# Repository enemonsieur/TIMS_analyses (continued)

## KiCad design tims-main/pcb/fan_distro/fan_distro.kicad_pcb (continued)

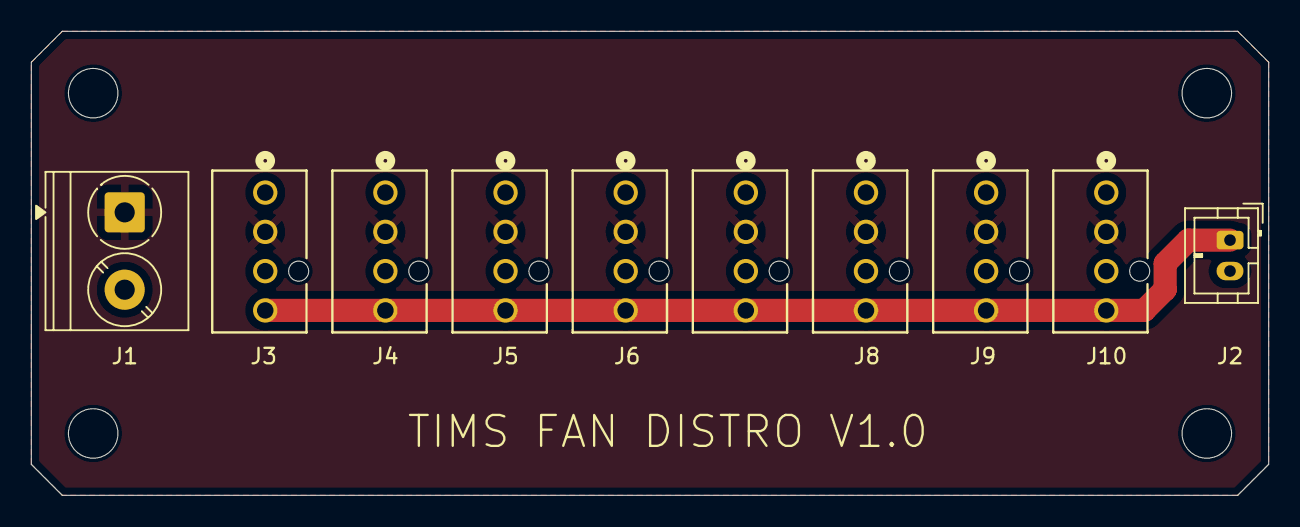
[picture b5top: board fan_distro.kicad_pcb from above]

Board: 2 copper layers, 80.0 x 30.0 mm, 10 parts (0 on the bottom side), 3 nets.

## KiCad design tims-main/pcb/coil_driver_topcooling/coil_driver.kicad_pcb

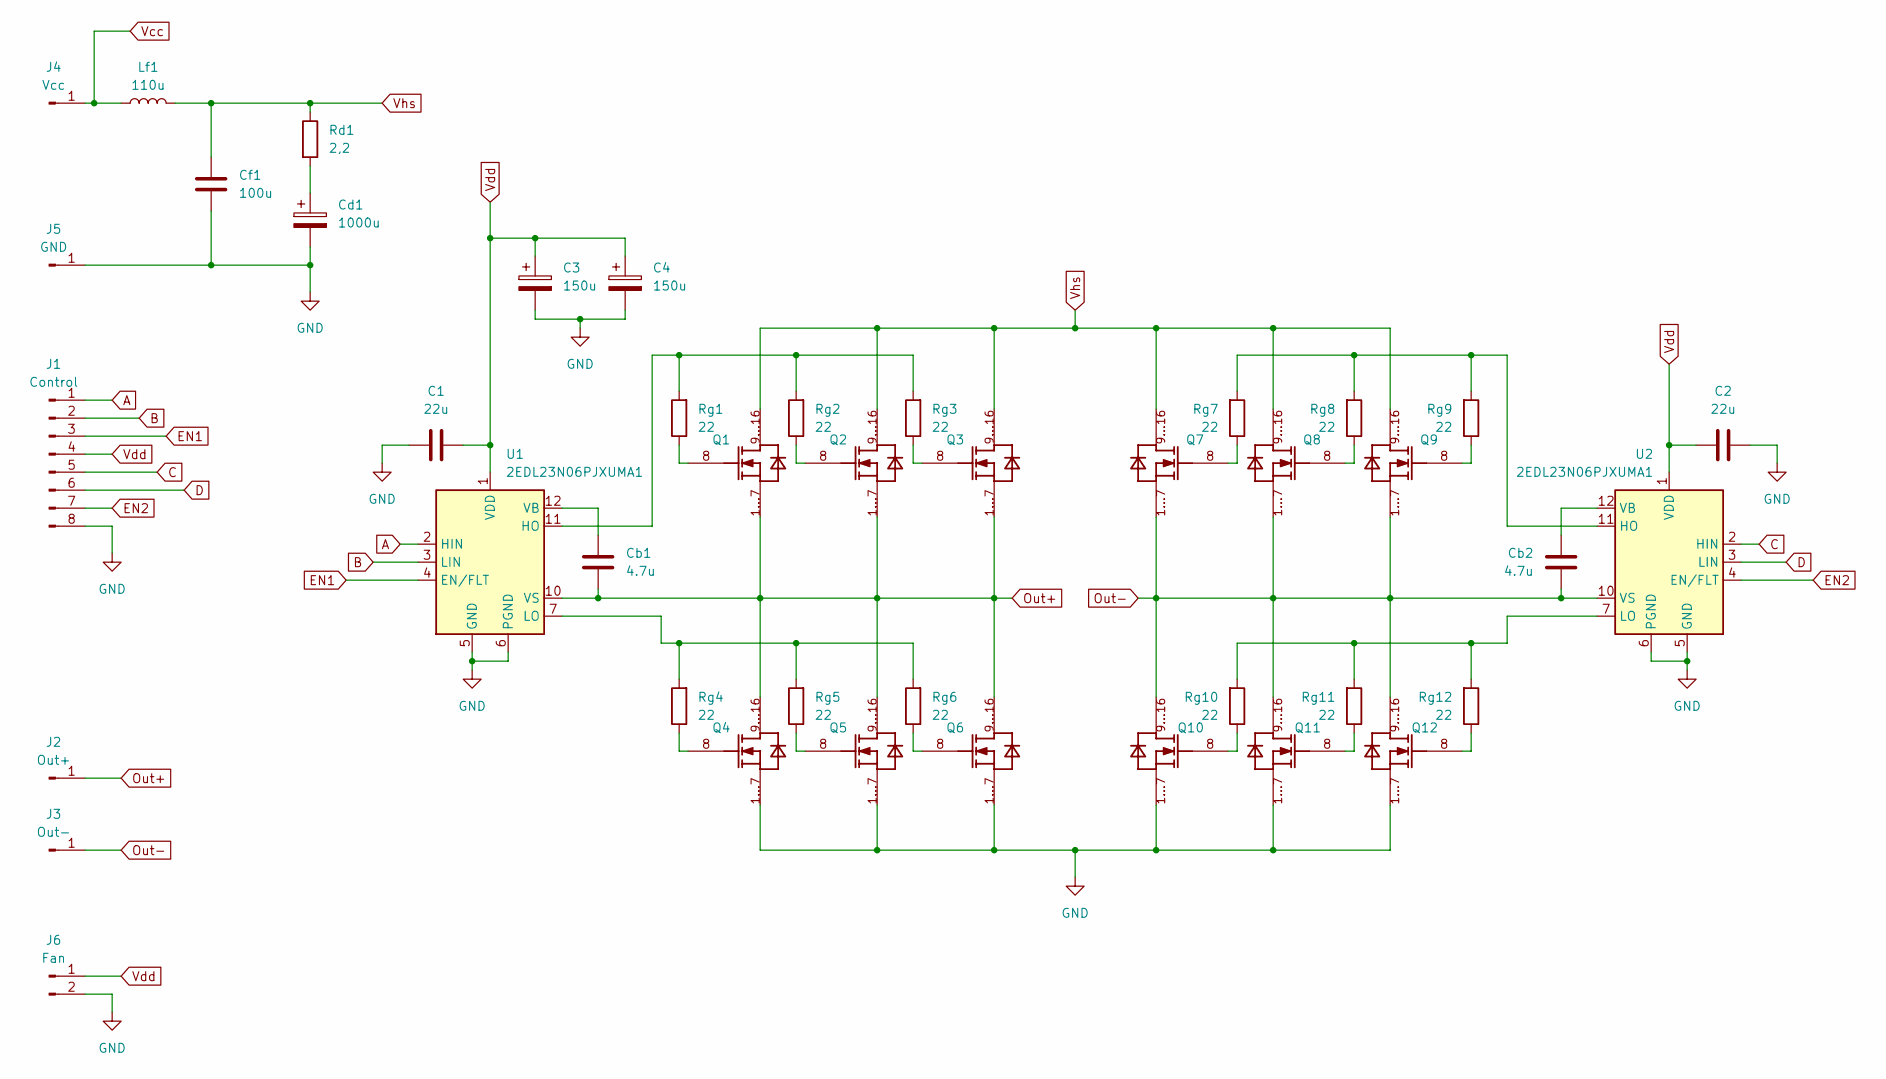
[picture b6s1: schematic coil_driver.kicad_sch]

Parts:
C1, C2: 22u; C_1206_3216Metric
C3, C4: 150u; CP_Radial_D10.0mm_P5.00mm
Cb1, Cb2: 4.7u; C_1206_3216Metric
Cd1: 1000u; CP_Radial_D30.0mm_P10.00mm_SnapIn
Cf1: 100u; 944U101K801AAM
J1: Control; JST_PH_B8B-PH-K_1x08_P2.00mm_Vertical
J2: Out+; Power_Pad
J3: Out-; Power_Pad
J4: Vcc; Power_Pad
J5: GND; Power_Pad
J6: Fan; JST_PH_B2B-PH-K_1x02_P2.00mm_Vertical
Lf1: 110u; IND_CPEX3635L-111MC
Q1, Q2, Q3, Q4, Q5, Q6, Q7, Q8, Q9, Q10, Q11, Q12: IPTC068N20NM6; SOIC120P1500X235-16N-1-V
Rd1: 2,2; SQMBW102R2J
Rg1, Rg2, Rg3, Rg4, Rg5, Rg6, Rg7, Rg8, Rg9, Rg10, Rg11, Rg12: 22; R_1206_3216Metric
U1, U2: 2EDL23N06PJXUMA1; SOIC-14_3.9x8.7mm_P1.27mm

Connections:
A: J1.1, U1.2 (HIN)
B: J1.2, U1.3 (LIN)
C: J1.5, U2.2 (HIN)
D: J1.6, U2.3 (LIN)
EN1: J1.3, U1.4 (EN/FLT)
EN2: J1.7, U2.4 (EN/FLT)
GND: C1.1, C2.1, C3.2, C4.2, Cd1.2, Cf1.2, J1.8, J5.1, J6.2, Q4.1 (S1), Q4.2 (S2), Q4.3 (S3), Q4.4 (S4), Q4.5 (S5), Q4.6 (S6), Q4.7 (S7), Q5.1 (S1), Q5.2 (S2), Q5.3 (S3), Q5.4 (S4), Q5.5 (S5), Q5.6 (S6), Q5.7 (S7), Q6.1 (S1), Q6.2 (S2), Q6.3 (S3), Q6.4 (S4), Q6.5 (S5), Q6.6 (S6), Q6.7 (S7), Q10.1 (S1), Q10.2 (S2), Q10.3 (S3), Q10.4 (S4), Q10.5 (S5), Q10.6 (S6), Q10.7 (S7), Q11.1 (S1), Q11.2 (S2), Q11.3 (S3), Q11.4 (S4), Q11.5 (S5), Q11.6 (S6), Q11.7 (S7), Q12.1 (S1), Q12.2 (S2), Q12.3 (S3), Q12.4 (S4), Q12.5 (S5), Q12.6 (S6), Q12.7 (S7), U1.5 (GND), U1.6 (PGND), U2.5 (GND), U2.6 (PGND)
unnamed: Cd1.1, Rd1.2
unnamed: Q1.8 (G), Rg1.1
unnamed: Q2.8 (G), Rg2.1
unnamed: Q3.8 (G), Rg3.1
unnamed: Q4.8 (G), Rg4.1
unnamed: Q5.8 (G), Rg5.1
unnamed: Q6.8 (G), Rg6.1
unnamed: Q7.8 (G), Rg7.1
unnamed: Q8.8 (G), Rg8.1
unnamed: Q9.8 (G), Rg9.1
unnamed: Q10.8 (G), Rg10.1
unnamed: Q11.8 (G), Rg11.1
unnamed: Q12.8 (G), Rg12.1
unnamed: Rg1.2, Rg2.2, Rg3.2, U1.11 (HO)
unnamed: Rg4.2, Rg5.2, Rg6.2, U1.7 (LO)
unnamed: Cb1.1, U1.12 (VB)
unnamed: Rg7.2, Rg8.2, Rg9.2, U2.11 (HO)
unnamed: Rg10.2, Rg11.2, Rg12.2, U2.7 (LO)
unnamed: Cb2.1, U2.12 (VB)
Out+: Cb1.2, J2.1, Q1.1 (S1), Q1.2 (S2), Q1.3 (S3), Q1.4 (S4), Q1.5 (S5), Q1.6 (S6), Q1.7 (S7), Q2.1 (S1), Q2.2 (S2), Q2.3 (S3), Q2.4 (S4), Q2.5 (S5), Q2.6 (S6), Q2.7 (S7), Q3.1 (S1), Q3.2 (S2), Q3.3 (S3), Q3.4 (S4), Q3.5 (S5), Q3.6 (S6), Q3.7 (S7), Q4.9 (D1), Q4.10 (D2), Q4.11 (D3), Q4.12 (D4), Q4.13 (D5), Q4.14 (D6), Q4.15 (D7), Q4.16 (D8), Q5.9 (D1), Q5.10 (D2), Q5.11 (D3), Q5.12 (D4), Q5.13 (D5), Q5.14 (D6), Q5.15 (D7), Q5.16 (D8), Q6.9 (D1), Q6.10 (D2), Q6.11 (D3), Q6.12 (D4), Q6.13 (D5), Q6.14 (D6), Q6.15 (D7), Q6.16 (D8), U1.10 (VS)
Out-: Cb2.2, J3.1, Q7.1 (S1), Q7.2 (S2), Q7.3 (S3), Q7.4 (S4), Q7.5 (S5), Q7.6 (S6), Q7.7 (S7), Q8.1 (S1), Q8.2 (S2), Q8.3 (S3), Q8.4 (S4), Q8.5 (S5), Q8.6 (S6), Q8.7 (S7), Q9.1 (S1), Q9.2 (S2), Q9.3 (S3), Q9.4 (S4), Q9.5 (S5), Q9.6 (S6), Q9.7 (S7), Q10.9 (D1), Q10.10 (D2), Q10.11 (D3), Q10.12 (D4), Q10.13 (D5), Q10.14 (D6), Q10.15 (D7), Q10.16 (D8), Q11.9 (D1), Q11.10 (D2), Q11.11 (D3), Q11.12 (D4), Q11.13 (D5), Q11.14 (D6), Q11.15 (D7), Q11.16 (D8), Q12.9 (D1), Q12.10 (D2), Q12.11 (D3), Q12.12 (D4), Q12.13 (D5), Q12.14 (D6), Q12.15 (D7), Q12.16 (D8), U2.10 (VS)
Vcc: J4.1, Lf1.1
Vdd: C1.2, C2.2, C3.1, C4.1, J1.4, J6.1, U1.1 (VDD), U2.1 (VDD)
Vhs: Cf1.1, Lf1.2, Q1.9 (D1), Q1.10 (D2), Q1.11 (D3), Q1.12 (D4), Q1.13 (D5), Q1.14 (D6), Q1.15 (D7), Q1.16 (D8), Q2.9 (D1), Q2.10 (D2), Q2.11 (D3), Q2.12 (D4), Q2.13 (D5), Q2.14 (D6), Q2.15 (D7), Q2.16 (D8), Q3.9 (D1), Q3.10 (D2), Q3.11 (D3), Q3.12 (D4), Q3.13 (D5), Q3.14 (D6), Q3.15 (D7), Q3.16 (D8), Q7.9 (D1), Q7.10 (D2), Q7.11 (D3), Q7.12 (D4), Q7.13 (D5), Q7.14 (D6), Q7.15 (D7), Q7.16 (D8), Q8.9 (D1), Q8.10 (D2), Q8.11 (D3), Q8.12 (D4), Q8.13 (D5), Q8.14 (D6), Q8.15 (D7), Q8.16 (D8), Q9.9 (D1), Q9.10 (D2), Q9.11 (D3), Q9.12 (D4), Q9.13 (D5), Q9.14 (D6), Q9.15 (D7), Q9.16 (D8), Rd1.1

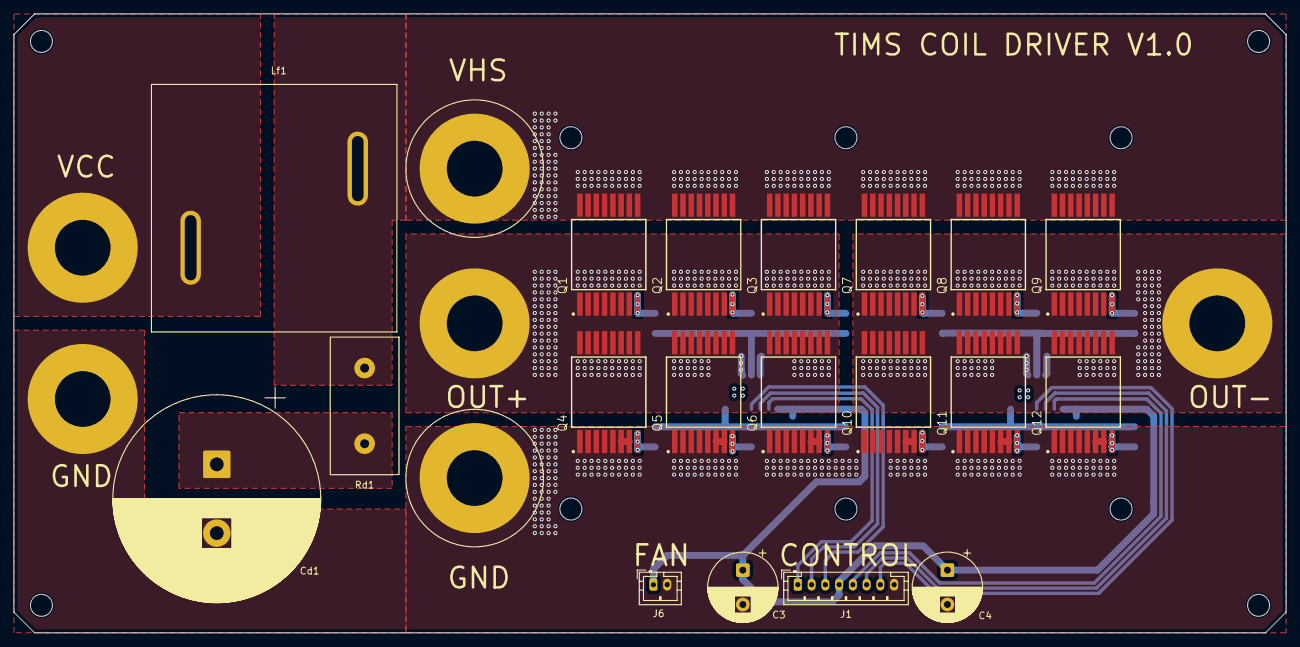
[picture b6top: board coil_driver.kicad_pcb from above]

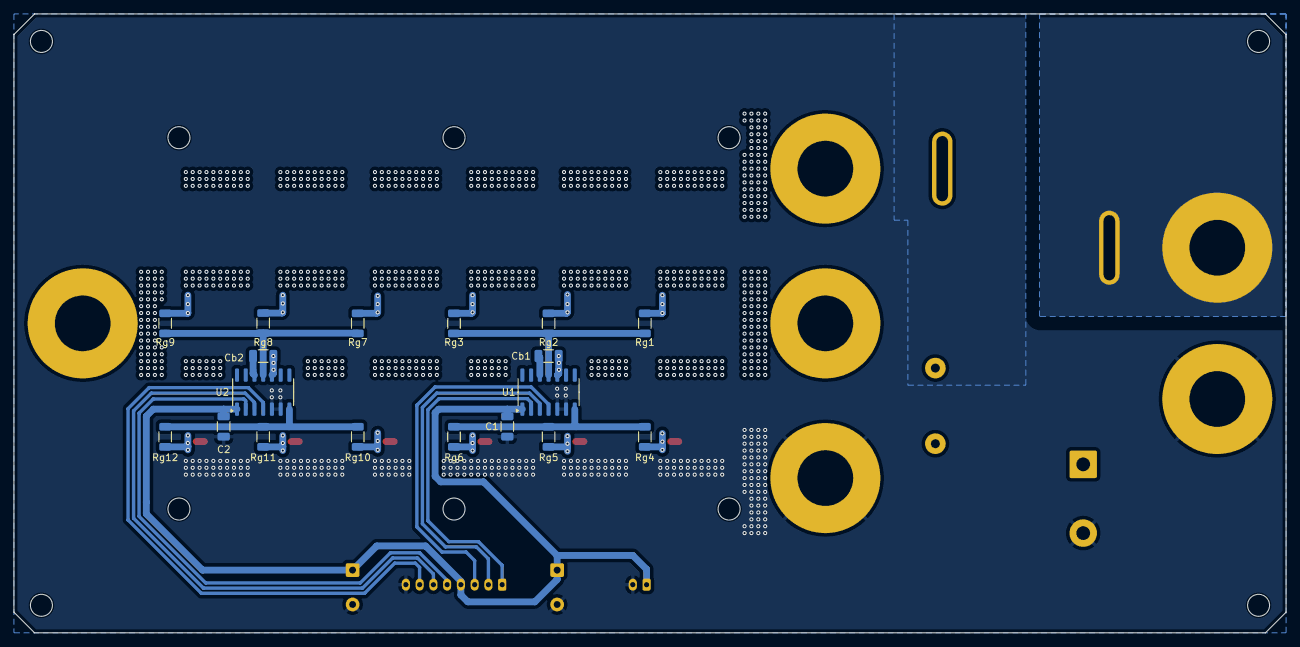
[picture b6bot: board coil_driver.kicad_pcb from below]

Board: 4 copper layers, 185.0 x 90.0 mm, 42 parts (18 on the bottom side), 31 nets.

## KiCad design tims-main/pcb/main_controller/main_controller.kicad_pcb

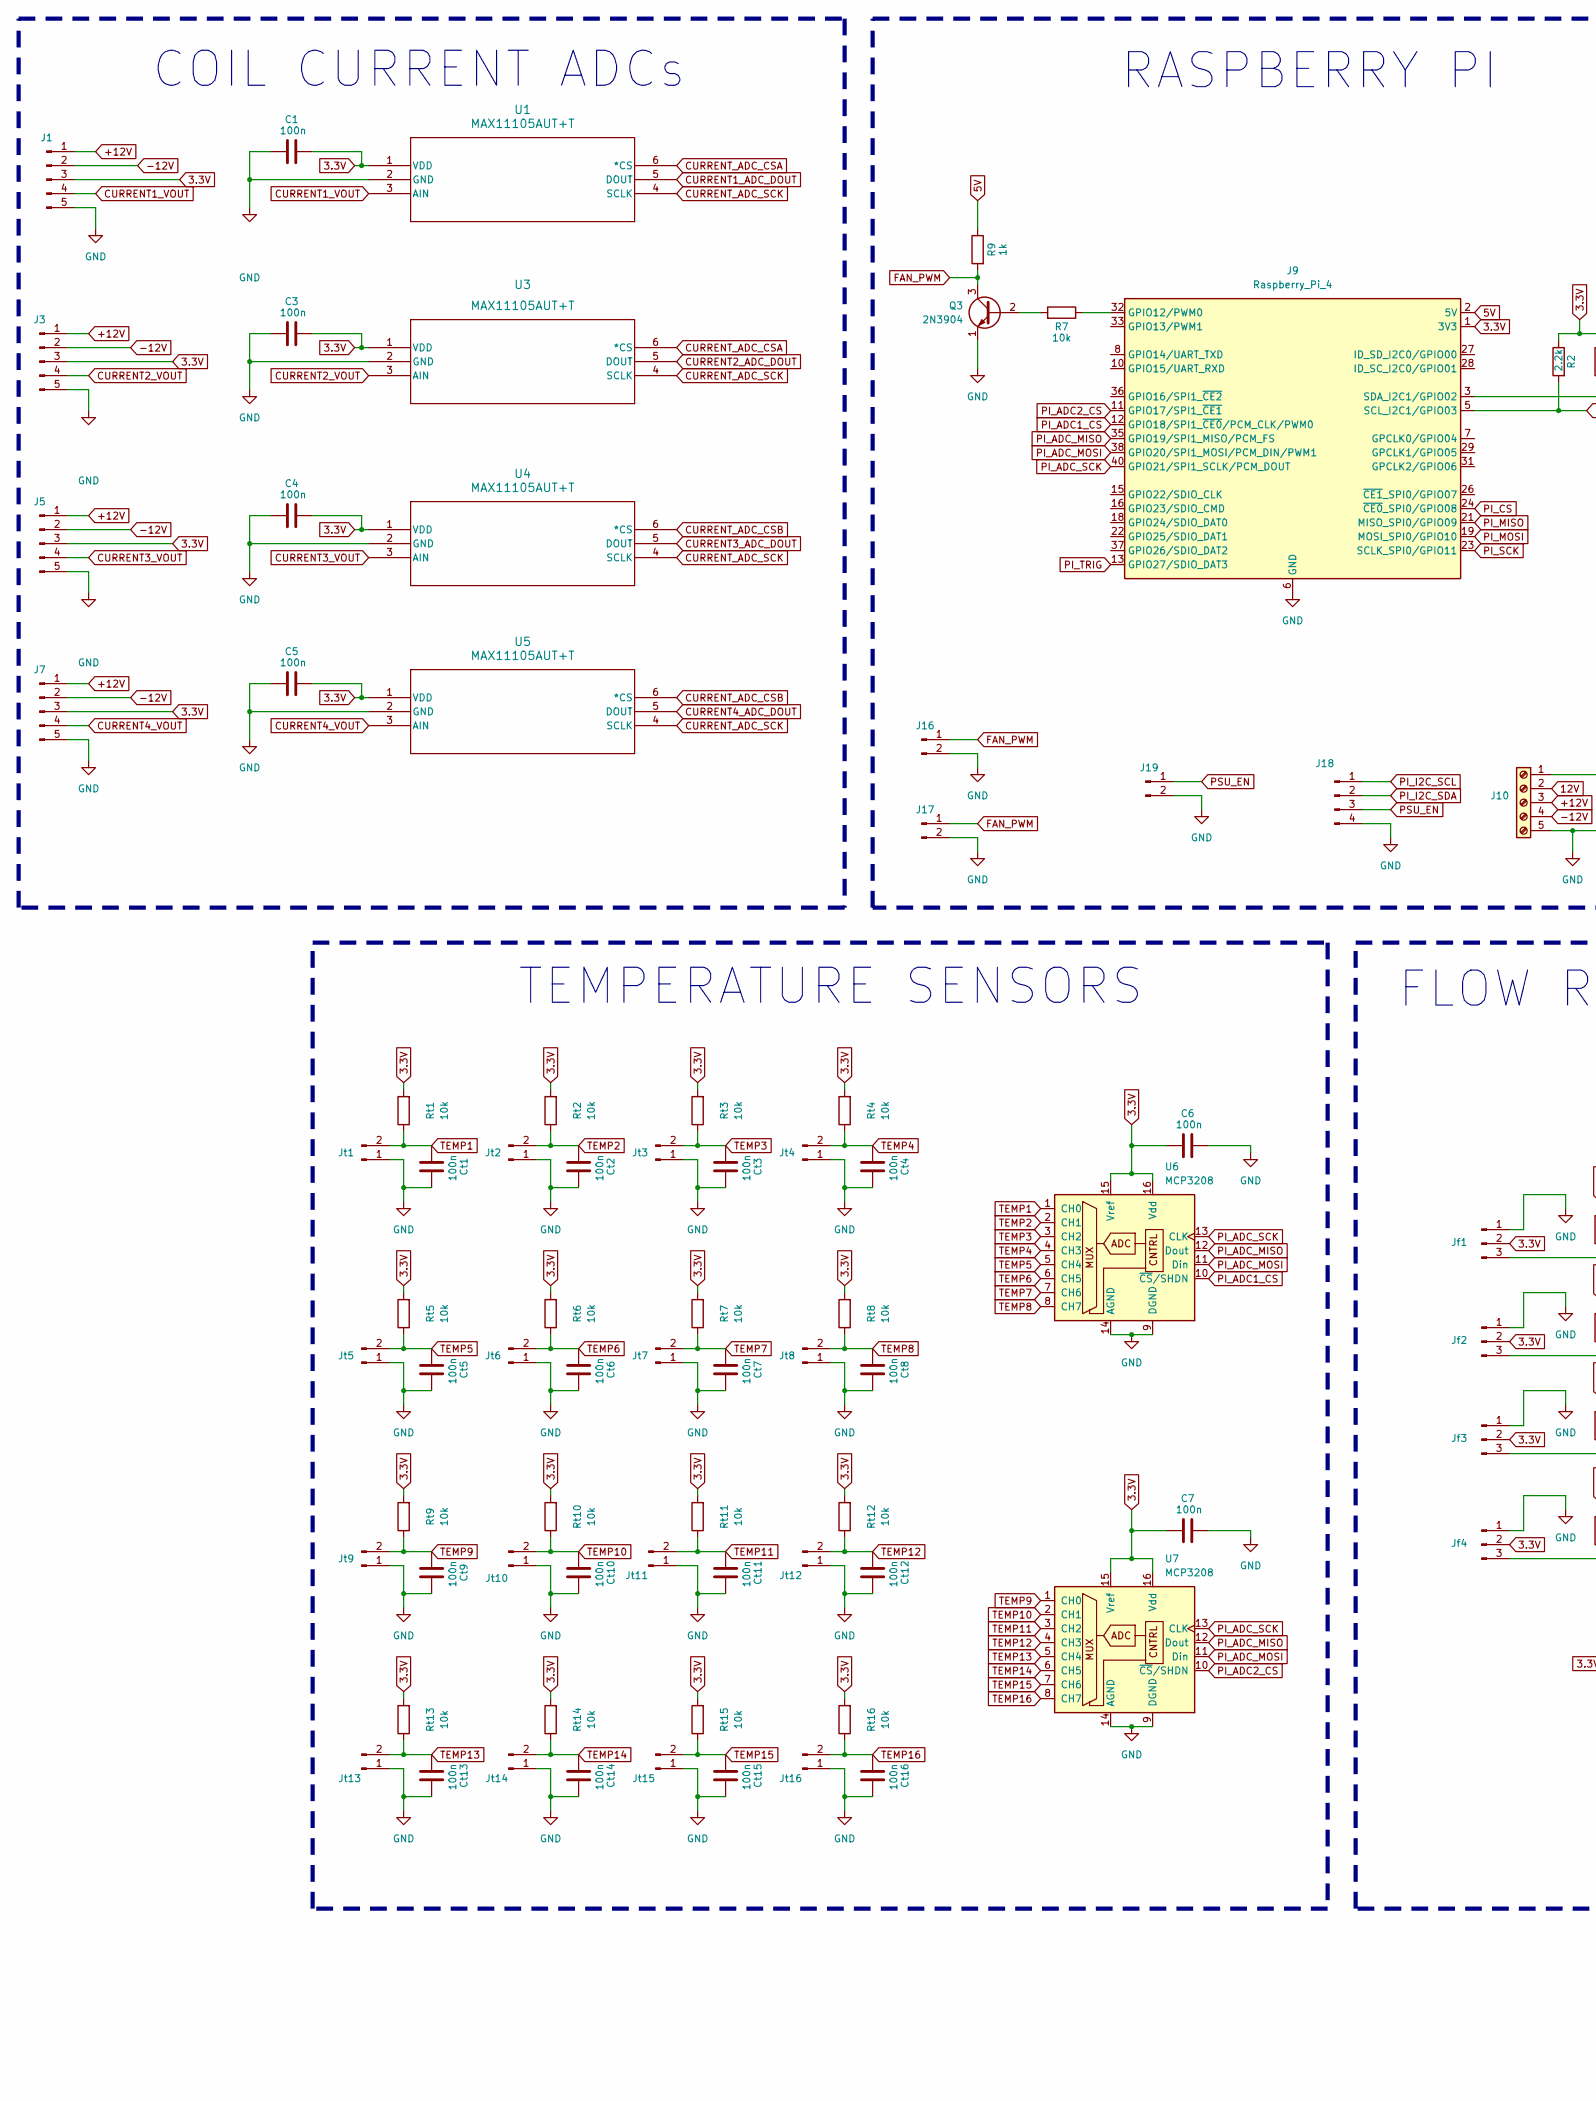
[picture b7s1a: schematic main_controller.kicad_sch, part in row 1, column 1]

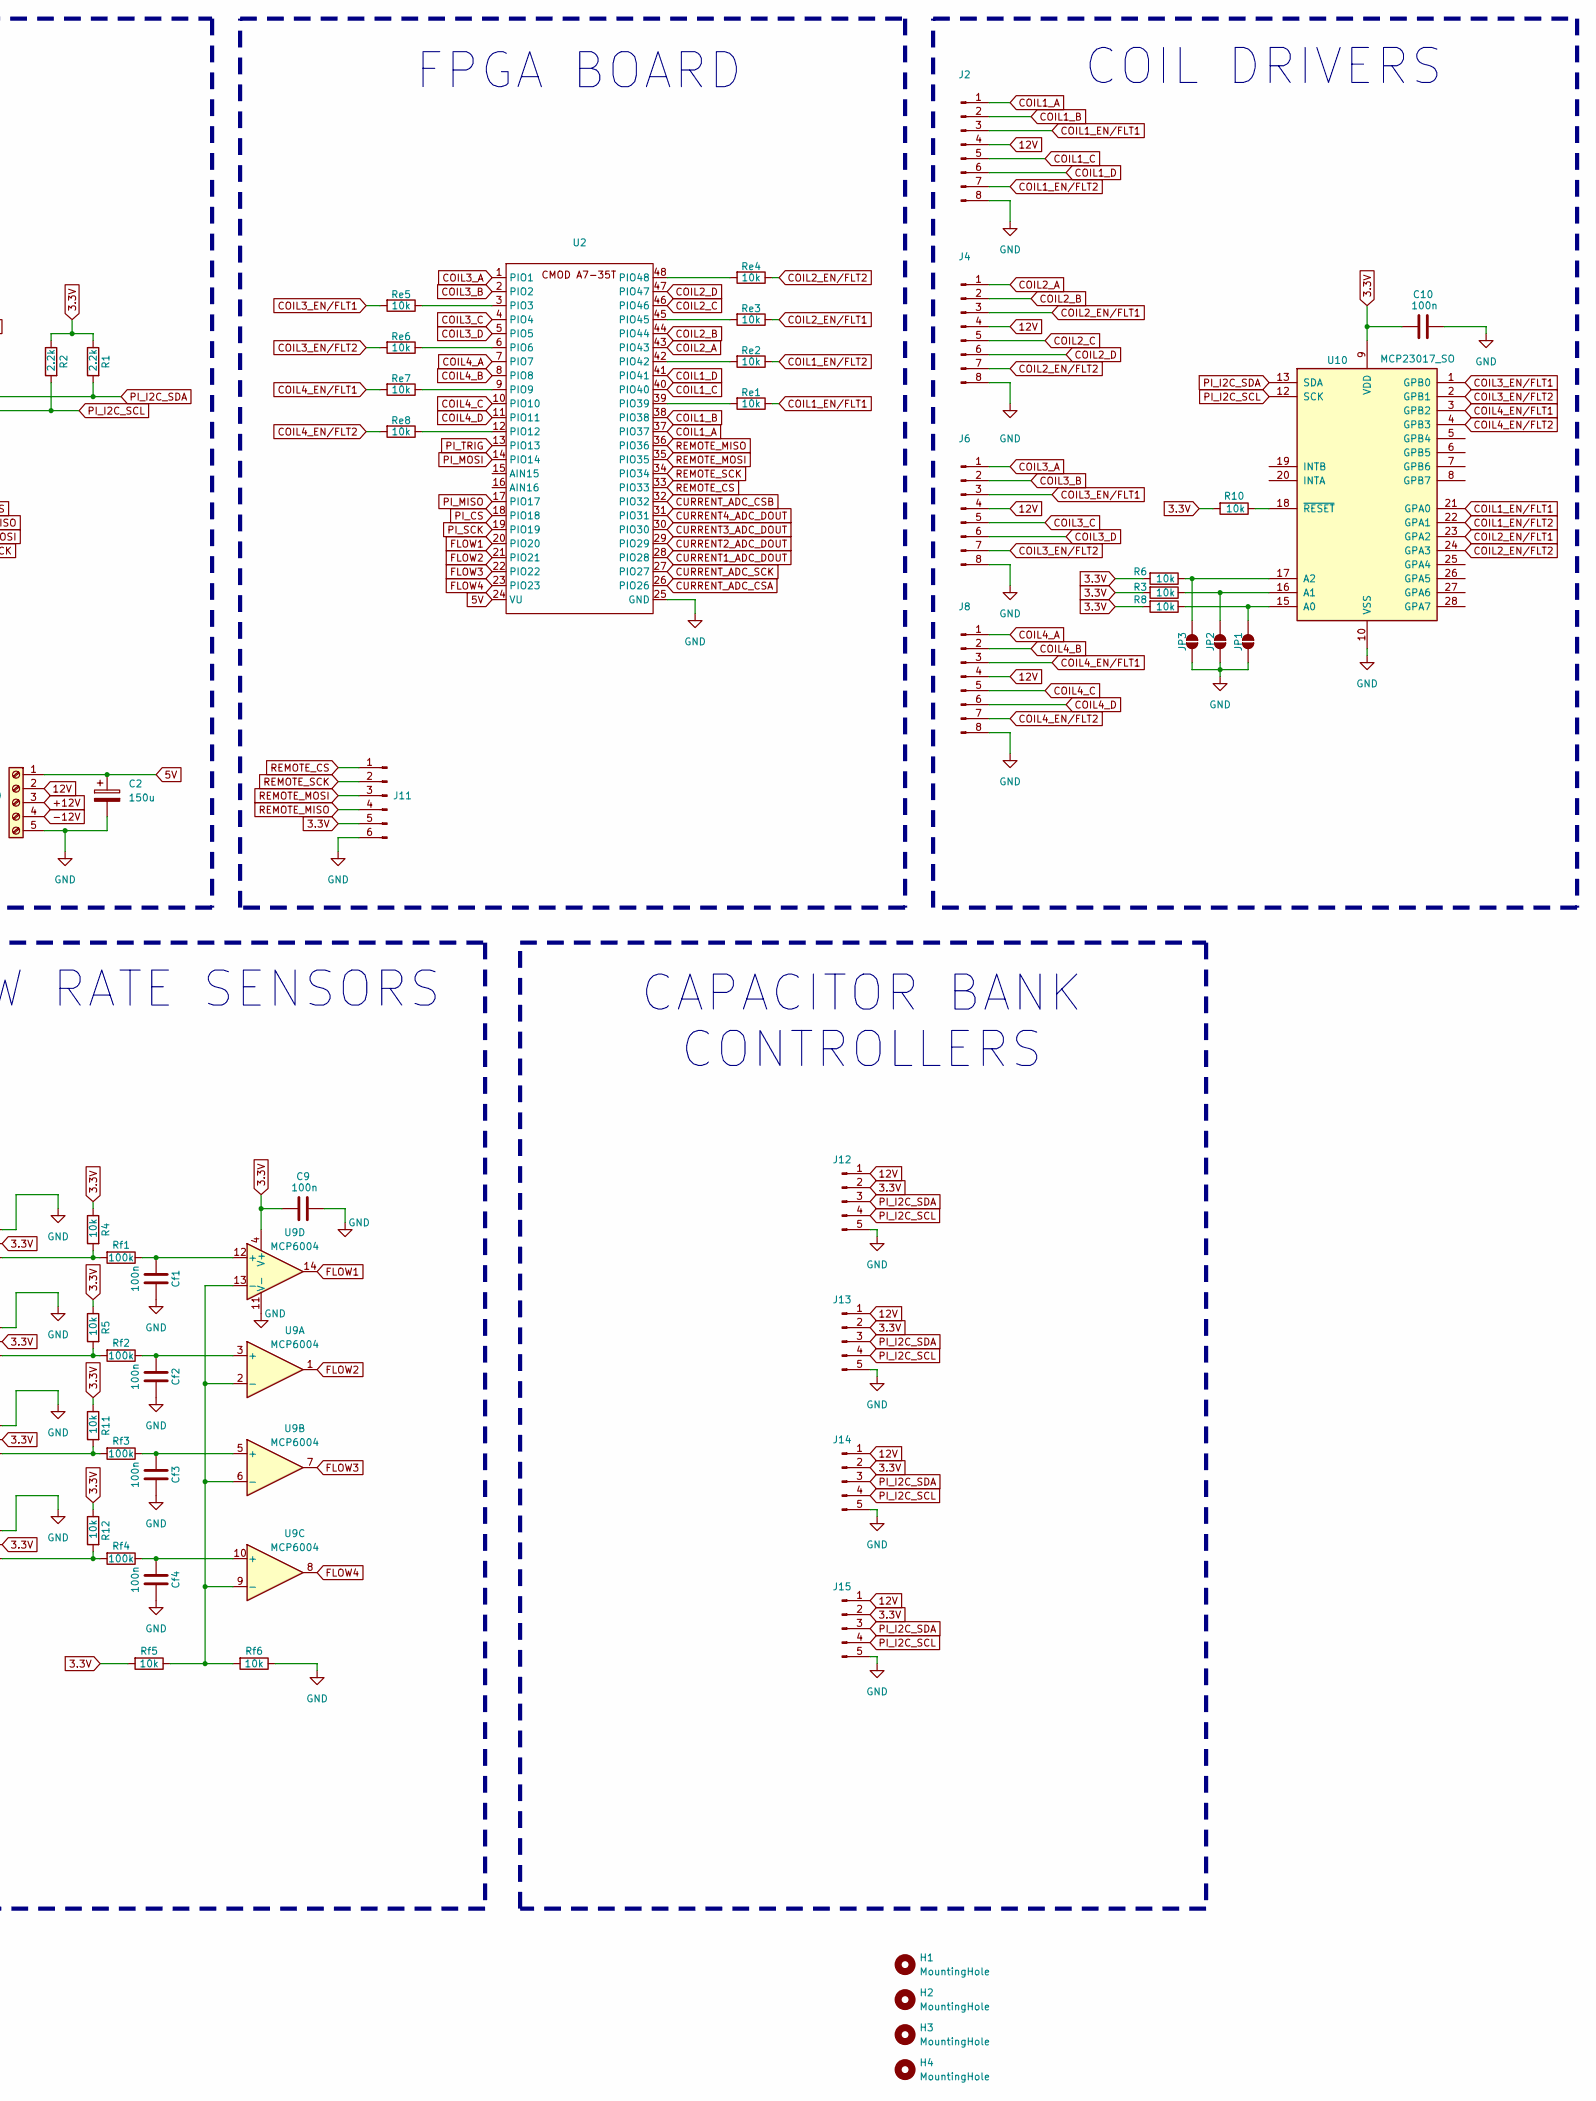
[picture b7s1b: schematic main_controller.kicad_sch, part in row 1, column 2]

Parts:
C1, C3, C4, C5, C6, C7, C9, C10: 100n; C_1206_3216Metric
C2: 150u; CP_Radial_D10.0mm_P5.00mm
Cf1, Cf2, Cf3, Cf4: 100n; C_1206_3216Metric
Ct1, Ct2, Ct3, Ct4, Ct5, Ct6, Ct7, Ct8, Ct9, Ct10, Ct11, Ct12, Ct13, Ct14, Ct15, Ct16: 100n; C_1206_3216Metric
H1, H2, H3, H4: MountingHole; MountingHole_3.2mm_M3
J1, J3, J5, J7, J12, J13, J14, J15: Conn_01x05_Pin; JST_PH_B5B-PH-K_1x05_P2.00mm_Vertical
J2, J4, J6, J8: Control; JST_PH_B8B-PH-K_1x08_P2.00mm_Vertical
J9: Raspberry_Pi_4; PinSocket_2x20_P2.54mm_Vertical
J10: TerminalBlock_Phoenix_PT-1,5-5-5.0-H_1x05_P5.00mm_Horizontal
J11: Conn_01x06_Pin; JST_PH_B6B-PH-K_1x06_P2.00mm_Vertical
J16, J17, J19: Conn_01x02_Pin; JST_PH_B2B-PH-K_1x02_P2.00mm_Vertical
J18: Conn_01x04_Pin; JST_PH_B4B-PH-K_1x04_P2.00mm_Vertical
JP1, JP2, JP3: SolderJumper-2_P1.3mm_Open_TrianglePad1.0x1.5mm
Jf1, Jf2, Jf3, Jf4: Conn_01x03_Pin; Molex_KK-254_AE-6410-03A_1x03_P2.54mm_Vertical
Jt1, Jt2, Jt3, Jt4, Jt5, Jt6, Jt7, Jt8, Jt9, Jt10, Jt11, Jt12, Jt13, Jt14, Jt15, Jt16: Conn_01x02_Pin; PinHeader_1x02_P2.54mm_Vertical
Q3: 2N3904; SOT-23
R1, R2: 2.2k; R_1206_3216Metric
R3, R4, R5, R6, R7, R8, R10, R11, R12: 10k; R_1206_3216Metric
R9: 1k; R_1206_3216Metric
Re1, Re2, Re3, Re4, Re5, Re6, Re7, Re8: 10k; R_1206_3216Metric
Rf1, Rf2, Rf3, Rf4: 100k; R_1206_3216Metric
Rf5, Rf6: 10k; R_1206_3216Metric
Rt1, Rt2, Rt3, Rt4, Rt5, Rt6, Rt7, Rt8, Rt9, Rt10, Rt11, Rt12, Rt13, Rt14, Rt15, Rt16: 10k; R_1206_3216Metric
U1, U3, U4, U5: MAX11105AUT+T; SOT-23-6
U2: CMOD A7-35T
U6, U7: MCP3208; SOIC-16_3.9x9.9mm_P1.27mm
U9: MCP6004; SOIC-14_3.9x8.7mm_P1.27mm
U10: MCP23017_SO; SOIC-28W_7.5x17.9mm_P1.27mm

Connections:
3.3V: C1.1, C3.1, C4.1, C5.1, C6.2, C7.2, C9.2, C10.2, J1.3, J3.3, J5.3, J7.3, J9.1 (3V3), J9.17 (3V3), J11.5, J12.2, J13.2, J14.2, J15.2, Jf1.2, Jf2.2, Jf3.2, Jf4.2, R1.1, R2.1, R3.2, R4.1, R5.1, R6.2, R8.2, R10.2, R11.1, R12.1, Rf5.2, Rt1.2, Rt2.2, Rt3.2, Rt4.2, Rt5.2, Rt6.2, Rt7.2, Rt8.2, Rt9.2, Rt10.2, Rt11.2, Rt12.2, Rt13.2, Rt14.2, Rt15.2, Rt16.2, U1.1 (VDD), U3.1 (VDD), U4.1 (VDD), U5.1 (VDD), U6.15 (Vref), U6.16 (Vdd), U7.15 (Vref), U7.16 (Vdd), U9.4 (V+), U10.9 (VDD)
5V: C2.1, J9.2 (5V), J9.4 (5V), J10.1, R9.1, U2.24 (VU)
12V: J2.4, J4.4, J6.4, J8.4, J10.2, J12.1, J13.1, J14.1, J15.1
+12V: J1.1, J3.1, J5.1, J7.1, J10.3
-12V: J1.2, J3.2, J5.2, J7.2, J10.4
COIL1_A: J2.1, U2.37 (PIO37)
COIL1_B: J2.2, U2.38 (PIO38)
COIL1_C: J2.5, U2.40 (PIO40)
COIL1_D: J2.6, U2.41 (PIO41)
COIL1_EN/FLT1: J2.3, Re1.1, U10.21 (GPA0)
COIL1_EN/FLT2: J2.7, Re2.1, U10.22 (GPA1)
COIL2_A: J4.1, U2.43 (PIO43)
COIL2_B: J4.2, U2.44 (PIO44)
COIL2_C: J4.5, U2.46 (PIO46)
COIL2_D: J4.6, U2.47 (PIO47)
COIL2_EN/FLT1: J4.3, Re3.1, U10.23 (GPA2)
COIL2_EN/FLT2: J4.7, Re4.1, U10.24 (GPA3)
COIL3_A: J6.1, U2.1 (PIO1)
COIL3_B: J6.2, U2.2 (PIO2)
COIL3_C: J6.5, U2.4 (PIO4)
COIL3_D: J6.6, U2.5 (PIO5)
COIL3_EN/FLT1: J6.3, Re5.2, U10.1 (GPB0)
COIL3_EN/FLT2: J6.7, Re6.2, U10.2 (GPB1)
COIL4_A: J8.1, U2.7 (PIO7)
COIL4_B: J8.2, U2.8 (PIO8)
COIL4_C: J8.5, U2.10 (PIO10)
COIL4_D: J8.6, U2.11 (PIO11)
COIL4_EN/FLT1: J8.3, Re7.2, U10.3 (GPB2)
COIL4_EN/FLT2: J8.7, Re8.2, U10.4 (GPB3)
CURRENT1_ADC_DOUT: U1.5 (DOUT), U2.28 (PIO28)
CURRENT1_VOUT: J1.4, U1.3 (AIN)
CURRENT2_ADC_DOUT: U2.29 (PIO29), U3.5 (DOUT)
CURRENT2_VOUT: J3.4, U3.3 (AIN)
CURRENT3_ADC_DOUT: U2.30 (PIO30), U4.5 (DOUT)
CURRENT3_VOUT: J5.4, U4.3 (AIN)
CURRENT4_ADC_DOUT: U2.31 (PIO31), U5.5 (DOUT)
CURRENT4_VOUT: J7.4, U5.3 (AIN)
CURRENT_ADC_CSA: U1.6 (*CS), U2.26 (PIO26), U3.6 (*CS)
CURRENT_ADC_CSB: U2.32 (PIO32), U4.6 (*CS), U5.6 (*CS)
CURRENT_ADC_SCK: U1.4 (SCLK), U2.27 (PIO27), U3.4 (SCLK), U4.4 (SCLK), U5.4 (SCLK)
FAN_PWM: J16.1, J17.1, Q3.3 (C), R9.2
FLOW1: U2.20 (PIO20), U9.14
FLOW2: U2.21 (PIO21), U9.1
FLOW3: U2.22 (PIO22), U9.7
FLOW4: U2.23 (PIO23), U9.8
GND: C1.2, C2.2, C3.2, C4.2, C5.2, C6.1, C7.1, C9.1, C10.1, Cf1.1, Cf2.1, Cf3.1, Cf4.1, Ct1.1, Ct2.1, Ct3.1, Ct4.1, Ct5.1, Ct6.1, Ct7.1, Ct8.1, Ct9.1, Ct10.1, Ct11.1, Ct12.1, Ct13.1, Ct14.1, Ct15.1, Ct16.1, J1.5, J2.8, J3.5, J4.8, J5.5, J6.8, J7.5, J8.8, J9.6 (GND), J9.9 (GND), J9.14 (GND), J9.20 (GND), J9.25 (GND), J9.30 (GND), J9.34 (GND), J9.39 (GND), J10.5, J11.6, J12.5, J13.5, J14.5, J15.5, J16.2, J17.2, J18.4, J19.2, JP1.1 (A), JP2.1 (A), JP3.1 (A), Jf1.1, Jf2.1, Jf3.1, Jf4.1, Jt1.1, Jt2.1, Jt3.1, Jt4.1, Jt5.1, Jt6.1, Jt7.1, Jt8.1, Jt9.1, Jt10.1, Jt11.1, Jt12.1, Jt13.1, Jt14.1, Jt15.1, Jt16.1, Q3.1 (E), Rf6.1, U1.2 (GND), U2.25 (GND), U3.2 (GND), U4.2 (GND), U5.2 (GND), U6.9 (DGND), U6.14 (AGND), U7.9 (DGND), U7.14 (AGND), U9.11 (V-), U10.10 (VSS)
unnamed: J9.32 (GPIO12/PWM0), R7.1
unnamed: JP1.2 (B), R8.1, U10.15 (A0)
unnamed: JP2.2 (B), R3.1, U10.16 (A1)
unnamed: JP3.2 (B), R6.1, U10.17 (A2)
unnamed: Jf1.3, R4.2, Rf1.2
unnamed: Jf2.3, R5.2, Rf2.2
unnamed: Jf3.3, R11.2, Rf3.2
unnamed: Jf4.3, R12.2, Rf4.2
unnamed: Q3.2 (B), R7.2
unnamed: Re5.1, U2.3 (PIO3)
unnamed: Re6.1, U2.6 (PIO6)
unnamed: Re7.1, U2.9 (PIO9)
unnamed: Re8.1, U2.12 (PIO12)
unnamed: Re1.2, U2.39 (PIO39)
unnamed: Re2.2, U2.42 (PIO42)
unnamed: Re3.2, U2.45 (PIO45)
unnamed: Re4.2, U2.48 (PIO48)
unnamed: Cf2.2, Rf2.1, U9.3 (+)
unnamed: Rf5.1, Rf6.2, U9.2 (-), U9.6 (-), U9.9 (-), U9.13 (-)
unnamed: Cf3.2, Rf3.1, U9.5 (+)
unnamed: Cf4.2, Rf4.1, U9.10 (+)
unnamed: Cf1.2, Rf1.1, U9.12 (+)
unnamed: R10.1, U10.18 (~RESET)
PI_ADC1_CS: J9.12 (GPIO18/SPI1_~CE0/PCM_CLK/PWM0), U6.10 (~CS/SHDN)
PI_ADC2_CS: J9.11 (GPIO17/SPI1_~CE1), U7.10 (~CS/SHDN)
PI_ADC_MISO: J9.35 (GPIO19/SPI1_MISO/PCM_FS), U6.12 (Dout), U7.12 (Dout)
PI_ADC_MOSI: J9.38 (GPIO20/SPI1_MOSI/PCM_DIN/PWM1), U6.11 (Din), U7.11 (Din)
PI_ADC_SCK: J9.40 (GPIO21/SPI1_SCLK/PCM_DOUT), U6.13 (CLK), U7.13 (CLK)
PI_CS: J9.24 (~CE0_SPI0/GPIO08), U2.18 (PIO18)
PI_I2C_SCL: J9.5 (SCL_I2C1/GPIO03), J12.4, J13.4, J14.4, J15.4, J18.1, R2.2, U10.12 (SCK)
PI_I2C_SDA: J9.3 (SDA_I2C1/GPIO02), J12.3, J13.3, J14.3, J15.3, J18.2, R1.2, U10.13 (SDA)
PI_MISO: J9.21 (MISO_SPI0/GPIO09), U2.17 (PIO17)
PI_MOSI: J9.19 (MOSI_SPI0/GPIO10), U2.14 (PIO14)
PI_SCK: J9.23 (SCLK_SPI0/GPIO11), U2.19 (PIO19)
PI_TRIG: J9.13 (GPIO27/SDIO_DAT3), U2.13 (PIO13)
PSU_EN: J18.3, J19.1
REMOTE_CS: J11.1, U2.33 (PIO33)
REMOTE_MISO: J11.4, U2.36 (PIO36)
REMOTE_MOSI: J11.3, U2.35 (PIO35)
REMOTE_SCK: J11.2, U2.34 (PIO34)
TEMP1: Ct1.2, Jt1.2, Rt1.1, U6.1 (CH0)
TEMP2: Ct2.2, Jt2.2, Rt2.1, U6.2 (CH1)
TEMP3: Ct3.2, Jt3.2, Rt3.1, U6.3 (CH2)
TEMP4: Ct4.2, Jt4.2, Rt4.1, U6.4 (CH3)
TEMP5: Ct5.2, Jt5.2, Rt5.1, U6.5 (CH4)
TEMP6: Ct6.2, Jt6.2, Rt6.1, U6.6 (CH5)
TEMP7: Ct7.2, Jt7.2, Rt7.1, U6.7 (CH6)
TEMP8: Ct8.2, Jt8.2, Rt8.1, U6.8 (CH7)
TEMP9: Ct9.2, Jt9.2, Rt9.1, U7.1 (CH0)
TEMP10: Ct10.2, Jt10.2, Rt10.1, U7.2 (CH1)
TEMP11: Ct11.2, Jt11.2, Rt11.1, U7.3 (CH2)
TEMP12: Ct12.2, Jt12.2, Rt12.1, U7.4 (CH3)
TEMP13: Ct13.2, Jt13.2, Rt13.1, U7.5 (CH4)
TEMP14: Ct14.2, Jt14.2, Rt14.1, U7.6 (CH5)
TEMP15: Ct15.2, Jt15.2, Rt15.1, U7.7 (CH6)
TEMP16: Ct16.2, Jt16.2, Rt16.1, U7.8 (CH7)

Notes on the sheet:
COIL DRIVERS
COIL CURRENT ADCs
RASPBERRY PI
FLOW RATE SENSORS
TEMPERATURE SENSORS
FPGA BOARD
CAPACITOR BANK CONTROLLERS

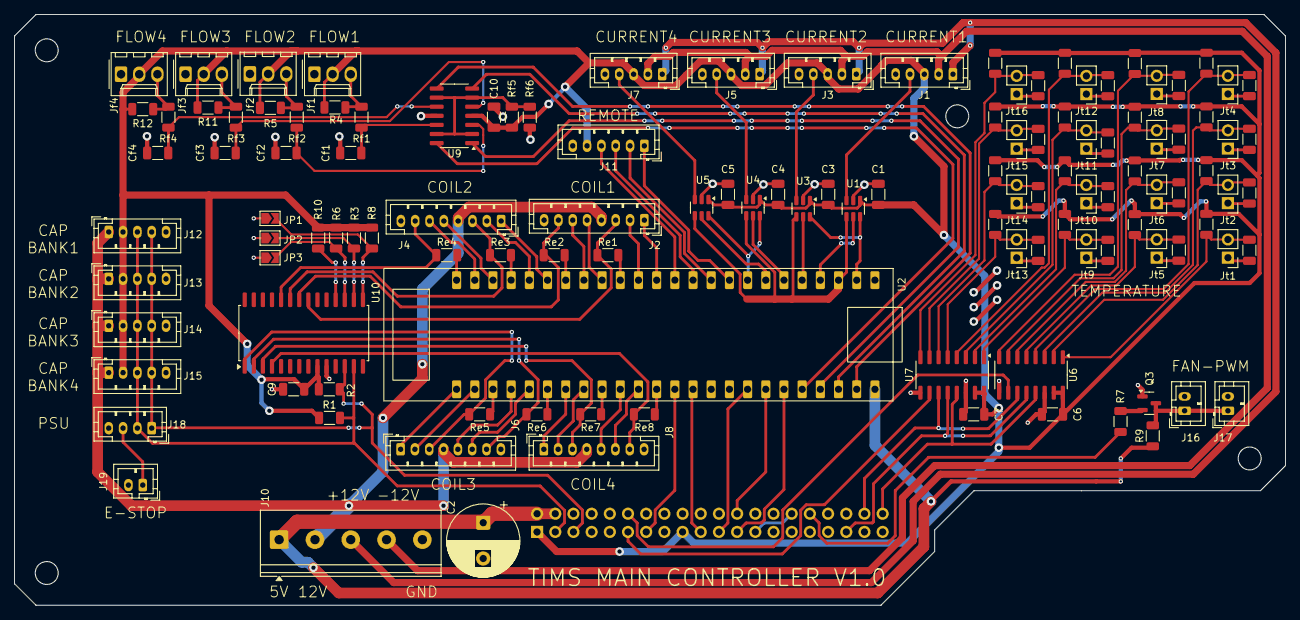
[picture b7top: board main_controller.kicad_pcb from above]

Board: 2 copper layers, 177.5 x 82.5 mm, 127 parts (1 on the bottom side), 102 nets.

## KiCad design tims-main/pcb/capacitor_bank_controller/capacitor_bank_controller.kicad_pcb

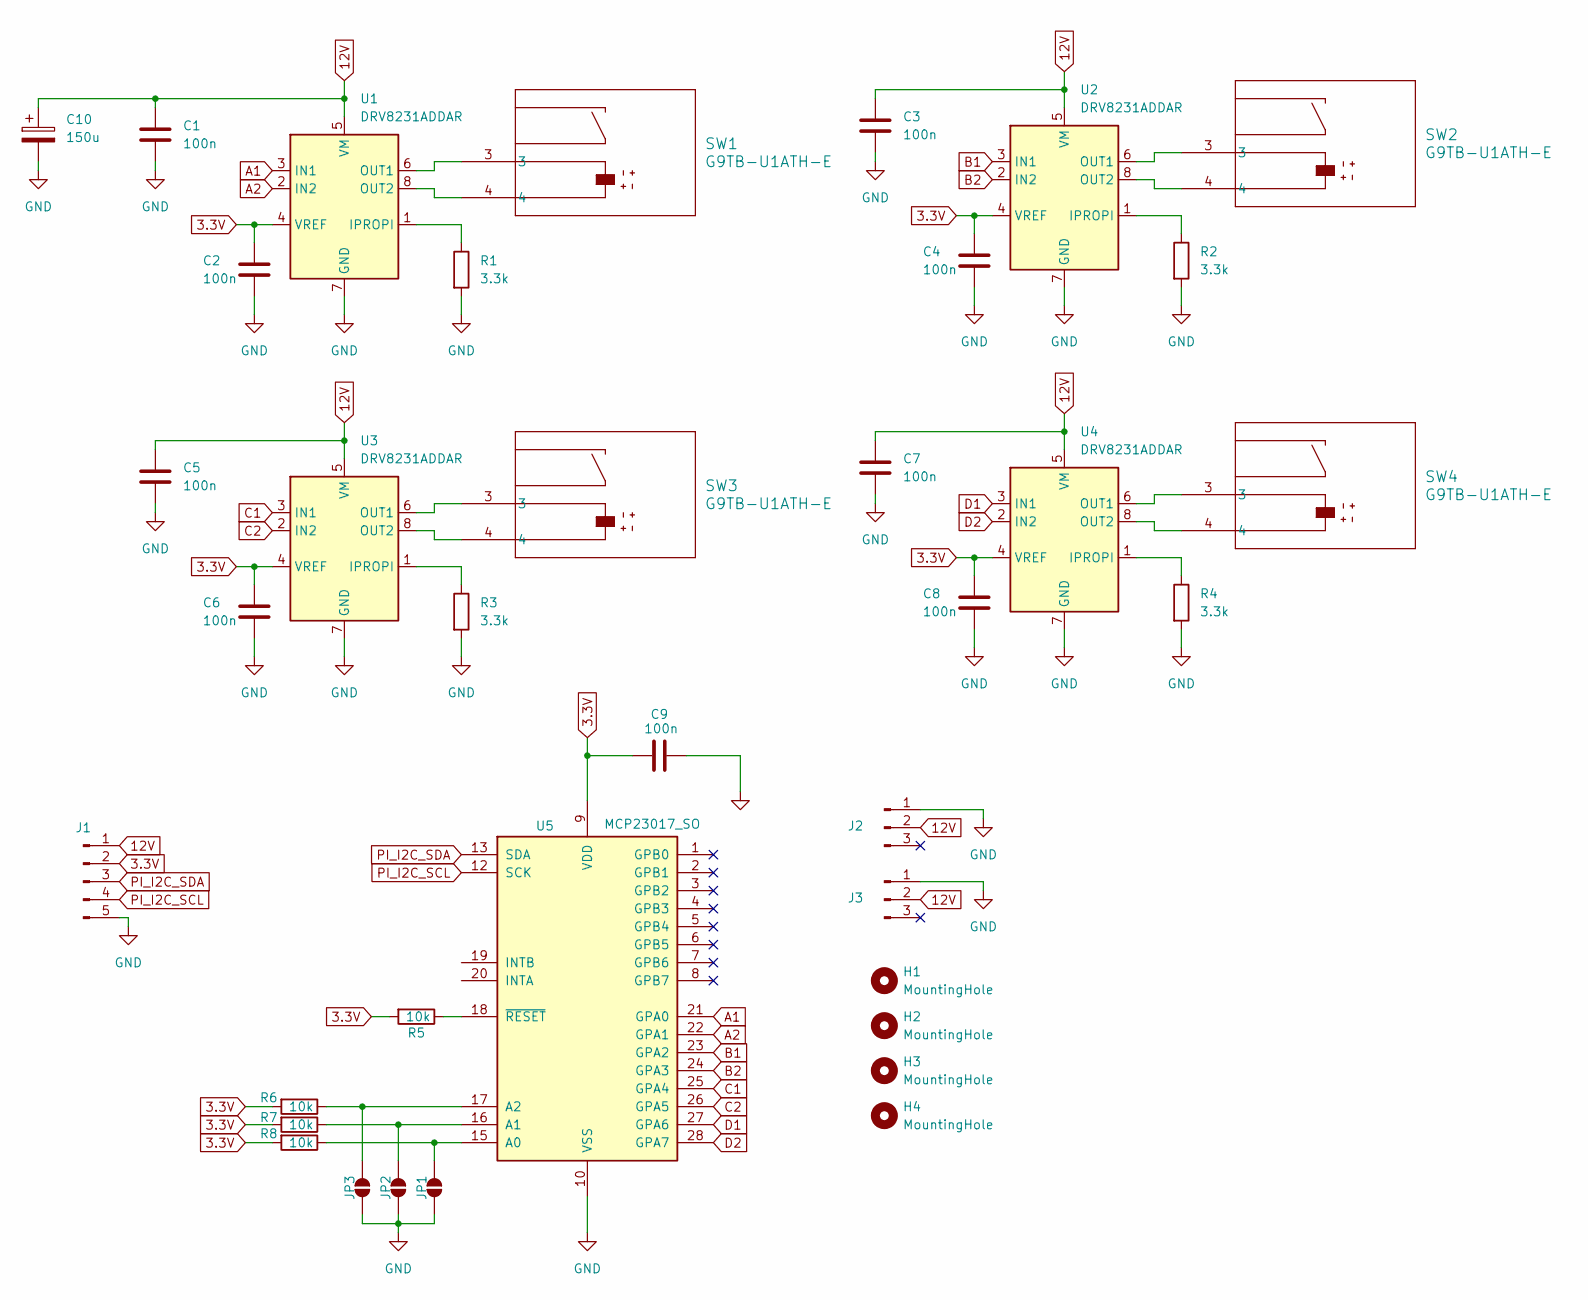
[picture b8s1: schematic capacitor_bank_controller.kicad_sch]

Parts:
C1, C2, C3, C4, C5, C6, C7, C8, C9: 100n; C_1206_3216Metric
C10: 150u; CP_Radial_D10.0mm_P5.00mm
H1, H2, H3, H4: MountingHole; MountingHole_4.3mm_M4
J1: Conn_01x05_Pin; JST_PH_B5B-PH-K_1x05_P2.00mm_Vertical
J2, J3: Conn_01x03_Pin; Molex_KK-254_AE-6410-03A_1x03_P2.54mm_Vertical
JP1, JP2, JP3: SolderJumper-2_P1.3mm_Open_TrianglePad1.0x1.5mm
R1, R2, R3, R4: 3.3k; R_1206_3216Metric
R5, R6, R7, R8: 10k; R_1206_3216Metric
SW1, SW2, SW3, SW4: G9TB-U1ATH-E
U1, U2, U3, U4: DRV8231ADDAR; TI_SO-PowerPAD-8
U5: MCP23017_SO; SOIC-28W_7.5x17.9mm_P1.27mm

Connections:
3.3V: C2.1, C4.1, C6.1, C8.1, C9.2, J1.2, R5.2, R6.2, R7.2, R8.2, U1.4 (VREF), U2.4 (VREF), U3.4 (VREF), U4.4 (VREF), U5.9 (VDD)
12V: C1.1, C3.1, C5.1, C7.1, C10.1, J1.1, J2.2, J3.2, U1.5 (VM), U2.5 (VM), U3.5 (VM), U4.5 (VM)
A1: U1.3 (IN1), U5.21 (GPA0)
A2: U1.2 (IN2), U5.22 (GPA1)
B1: U2.3 (IN1), U5.23 (GPA2)
B2: U2.2 (IN2), U5.24 (GPA3)
C1: U3.3 (IN1), U5.25 (GPA4)
C2: U3.2 (IN2), U5.26 (GPA5)
D1: U4.3 (IN1), U5.27 (GPA6)
D2: U4.2 (IN2), U5.28 (GPA7)
GND: C1.2, C2.2, C3.2, C4.2, C5.2, C6.2, C7.2, C8.2, C9.1, C10.2, J1.5, J2.1, J3.1, JP1.1 (A), JP2.1 (A), JP3.1 (A), R1.2, R2.2, R3.2, R4.2, U1.7 (GND), U1.9 (GND), U2.7 (GND), U2.9 (GND), U3.7 (GND), U3.9 (GND), U4.7 (GND), U4.9 (GND), U5.10 (VSS)
unnamed: JP1.2 (B), R8.1, U5.15 (A0)
unnamed: JP2.2 (B), R7.1, U5.16 (A1)
unnamed: JP3.2 (B), R6.1, U5.17 (A2)
unnamed: R1.1, U1.1 (IPROPI)
unnamed: SW1.3, U1.6 (OUT1)
unnamed: SW1.4, U1.8 (OUT2)
unnamed: R2.1, U2.1 (IPROPI)
unnamed: SW2.3, U2.6 (OUT1)
unnamed: SW2.4, U2.8 (OUT2)
unnamed: R3.1, U3.1 (IPROPI)
unnamed: SW3.3, U3.6 (OUT1)
unnamed: SW3.4, U3.8 (OUT2)
unnamed: R4.1, U4.1 (IPROPI)
unnamed: SW4.3, U4.6 (OUT1)
unnamed: SW4.4, U4.8 (OUT2)
unnamed: R5.1, U5.18 (~RESET)
PI_I2C_SCL: J1.4, U5.12 (SCK)
PI_I2C_SDA: J1.3, U5.13 (SDA)

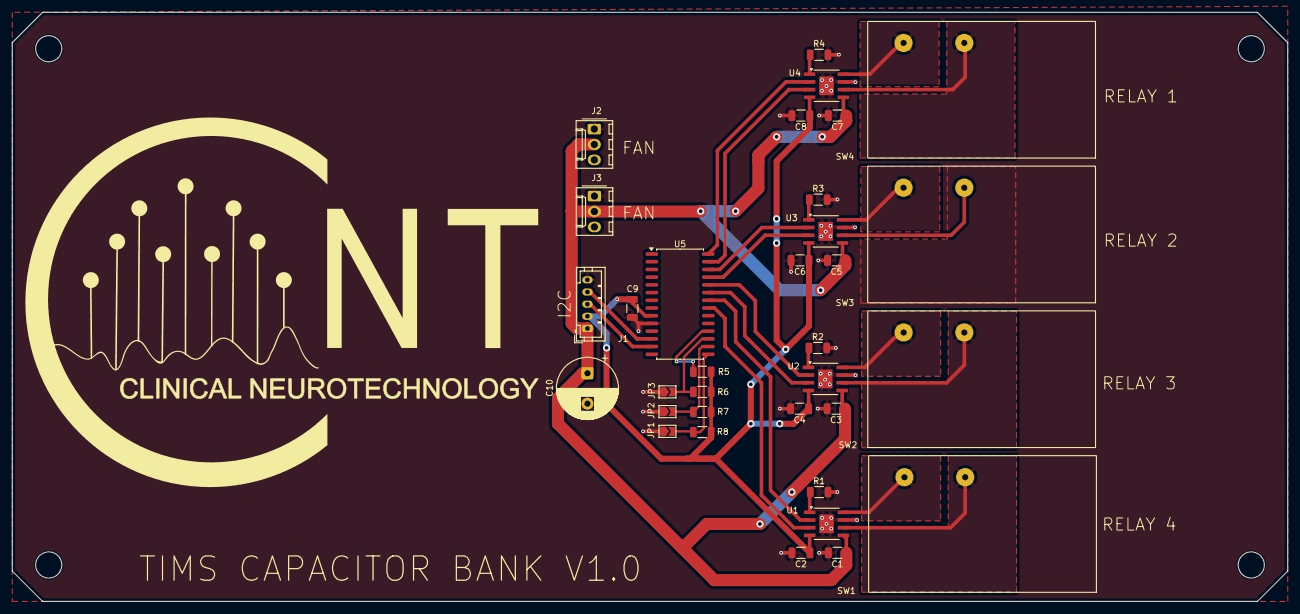
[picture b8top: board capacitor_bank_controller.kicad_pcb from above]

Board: 2 copper layers, 210.0 x 97.0 mm, 37 parts (0 on the bottom side), 29 nets.

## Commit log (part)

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2026-04-07 Experiment 6 tests and conclusions about feasability of our iTBS/cTBS protocol with TIMS
2026-04-28 EXP08: Add pulse onset alignment QC pass before artifact removal
    Detects per-pulse jitter via cross-correlation (−6 to +1 samples, std=1.72).
    Shows overlay of all 200 stim waveforms + lag histogram to validate alignment.
    Stops after QC plots; no epochs built yet. Fails current alignment criterion.
2026-05-05 Current work snapshot
